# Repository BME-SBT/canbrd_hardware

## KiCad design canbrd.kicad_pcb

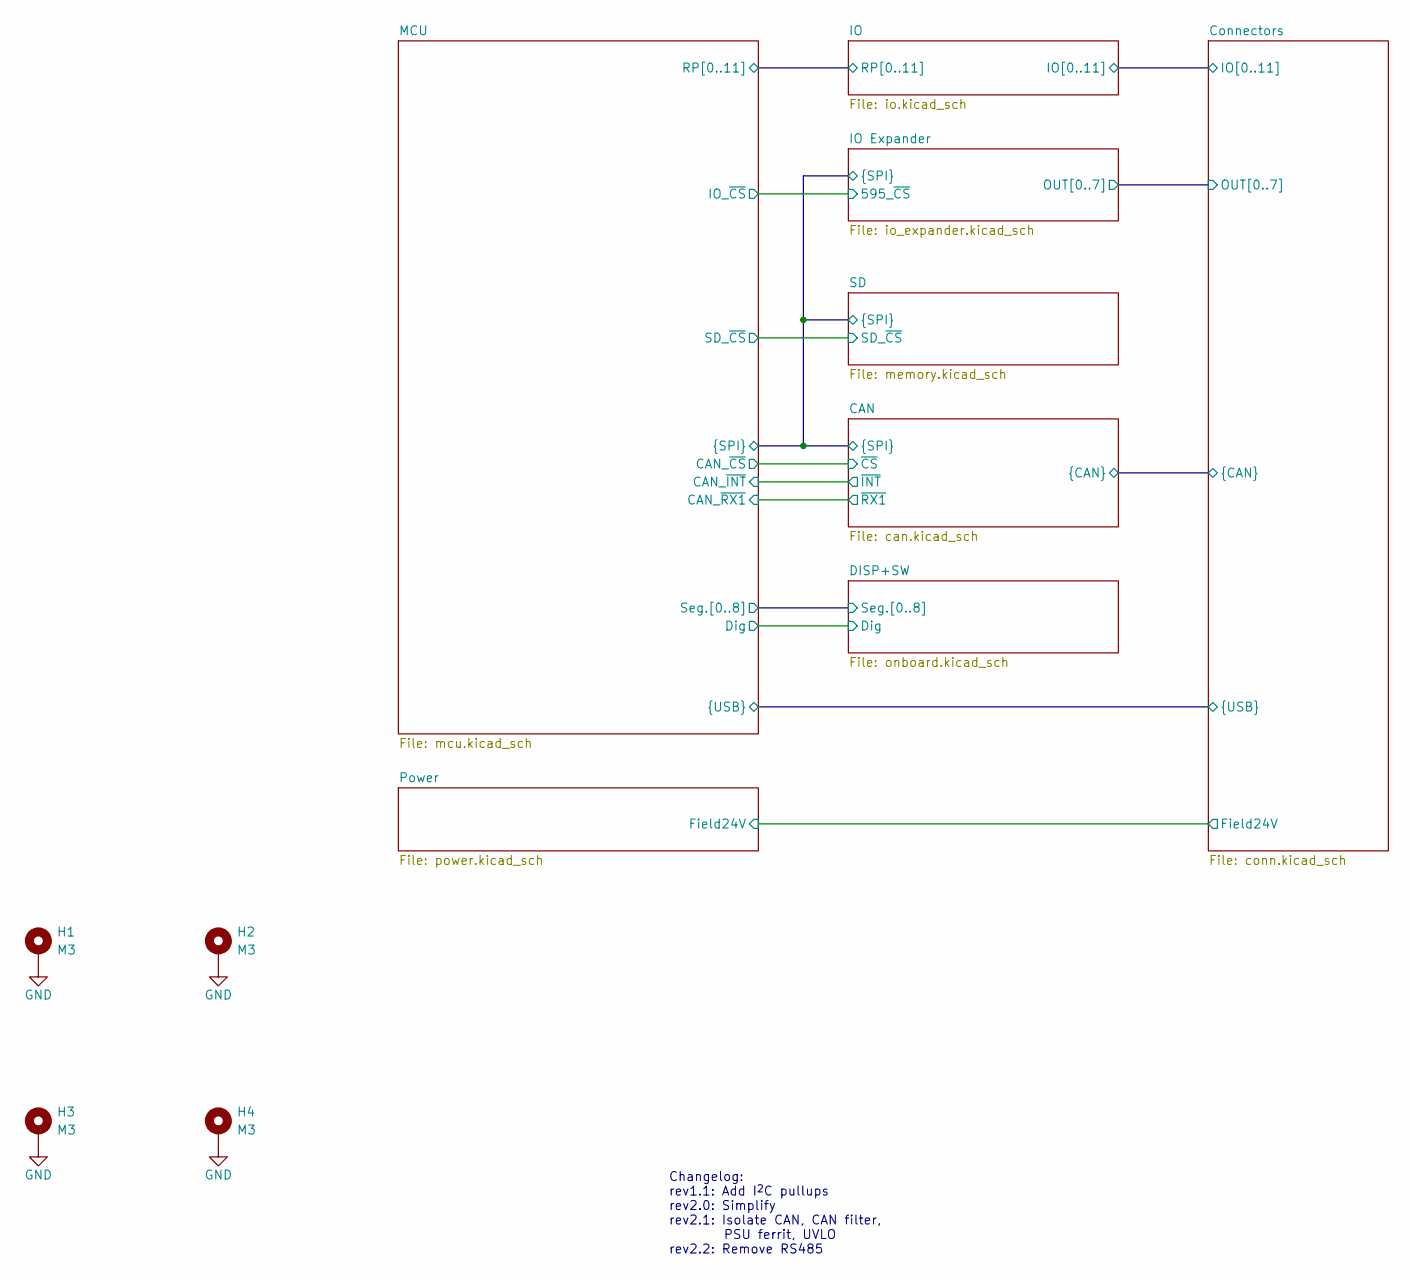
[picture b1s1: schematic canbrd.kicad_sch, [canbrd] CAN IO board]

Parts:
H1, H2, H3, H4: M3; MountingHole_3.2mm_M3_Pad_Via

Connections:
GND: H1.1, H2.1, H3.1, H4.1; also elsewhere on the board

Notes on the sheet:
Changelog: rev1.1: Add I^{2}C pullups rev2.0: Simplify rev2.1: Isolate CAN, CAN filter, PSU ferrit, UVLO rev2.2: Remove RS485

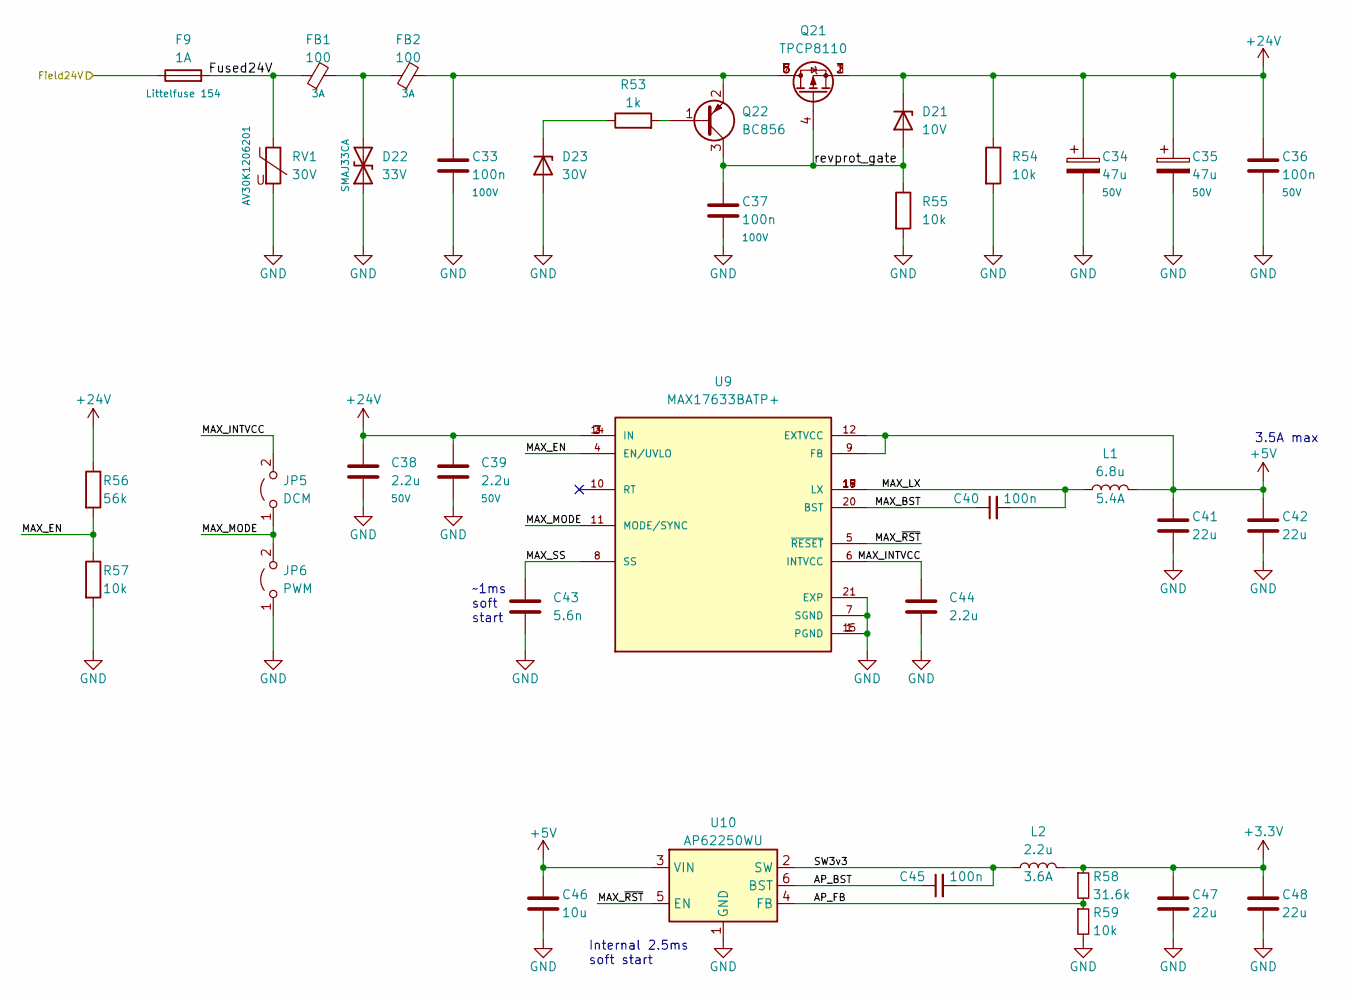
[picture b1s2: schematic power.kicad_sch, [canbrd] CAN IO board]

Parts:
C33, C37: 100n; C_1206_3216Metric; Voltage 100V
C34, C35: 47u; CP_Elec_8x6.5; Voltage 50V
C36: 100n; C_0805_2012Metric; Voltage 50V
C38, C39: 2.2u; C_1206_3216Metric; Voltage 50V
C40, C45: 100n; C_0603_1608Metric
C41, C42, C47, C48: 22u; C_0805_2012Metric
C43: 5.6n; C_0603_1608Metric
C44: 2.2u; C_0603_1608Metric
C46: 10u; C_0805_2012Metric
D21: 10V; D_SOD-123
D22: 33V; D_SMB
D23: 30V; D_SOD-123
F9: 1A; Littelfuse-154-2920
FB1, FB2: 100; L_1206_3216Metric
JP5: DCM; SolderJumper-2_P1.3mm_Open_TrianglePad1.0x1.5mm
JP6: PWM; SolderJumper-2_P1.3mm_Open_TrianglePad1.0x1.5mm
L1: 6.8u; L_Abracon_ASPI-0630LR
L2: 2.2u; L_Taiyo-Yuden_NR-50xx
Q21: TPCP8110; PS-8
Q22: BC856; SOT-23
R53: 1k; R_0603_1608Metric
R54, R55, R57, R59: 10k; R_0603_1608Metric
R56: 56k; R_0603_1608Metric
R58: 31.6k; R_0603_1608Metric
RV1: 30V; R_1206_3216Metric
U9: MAX17633BATP+; TQFN20-EP
U10: AP62250WU; TSOT26

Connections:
+3V3: C47.1, C48.1, L2.2, R58.1; also elsewhere on the board
+5V: C41.1, C42.1, C46.1, L1.2, U9.9 (FB), U9.12 (EXTVCC), U10.3 (VIN); also elsewhere on the board
+24V: C34.1, C35.1, C36.1, C38.1, C39.1, D21.1 (K), Q21.1 (S), Q21.2 (S), Q21.3 (S), R54.1, R56.1, U9.2 (IN), U9.3 (IN), U9.14 (IN); also elsewhere on the board
/Connectors/Field24V: F9.1; also elsewhere on the board
/Power/AP_BST: C45.1, U10.6 (BST)
/Power/AP_FB: R58.2, R59.1, U10.4 (FB)
/Power/Fused24V: F9.2, FB1.1, RV1.1
/Power/MAX_BST: C40.1, U9.20 (BST)
/Power/MAX_EN: R56.2, R57.1, U9.4 (EN/UVLO)
/Power/MAX_INTVCC: C44.1, JP5.2 (B), U9.6 (INTVCC)
/Power/MAX_LX: C40.2, L1.1, U9.17 (LX), U9.18 (LX), U9.19 (LX)
/Power/MAX_MODE: JP5.1 (A), JP6.2 (B), U9.11 (MODE/SYNC)
/Power/MAX_SS: C43.1, U9.8 (SS)
/Power/MAX_~RST: U9.5 (~RESET), U10.5 (EN)
/Power/SW3v3: C45.2, L2.1, U10.2 (SW)
/Power/revprot_gate: C37.1, D21.2 (A), Q21.4 (G), Q22.3 (C), R55.1
GND: C33.2, C34.2, C35.2, C36.2, C37.2, C38.2, C39.2, C41.2, C42.2, C43.2, C44.2, C46.2, C47.2, C48.2, D22.1 (A1), D23.2 (A), JP6.1 (A), R54.2, R55.2, R57.2, R59.2, RV1.2, U9.1 (PGND), U9.7 (SGND), U9.15 (PGND), U9.21 (EXP), U10.1 (GND); also elsewhere on the board
unnamed: C33.1, FB2.2, Q21.5 (D), Q21.6 (D), Q21.7 (D), Q21.8 (D), Q22.2 (E)
unnamed: D22.2 (A2), FB1.2, FB2.1
unnamed: D23.1 (K), R53.1
unnamed: Q22.1 (B), R53.2

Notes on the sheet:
~1ms soft start
3.5A max
Internal 2.5ms soft start

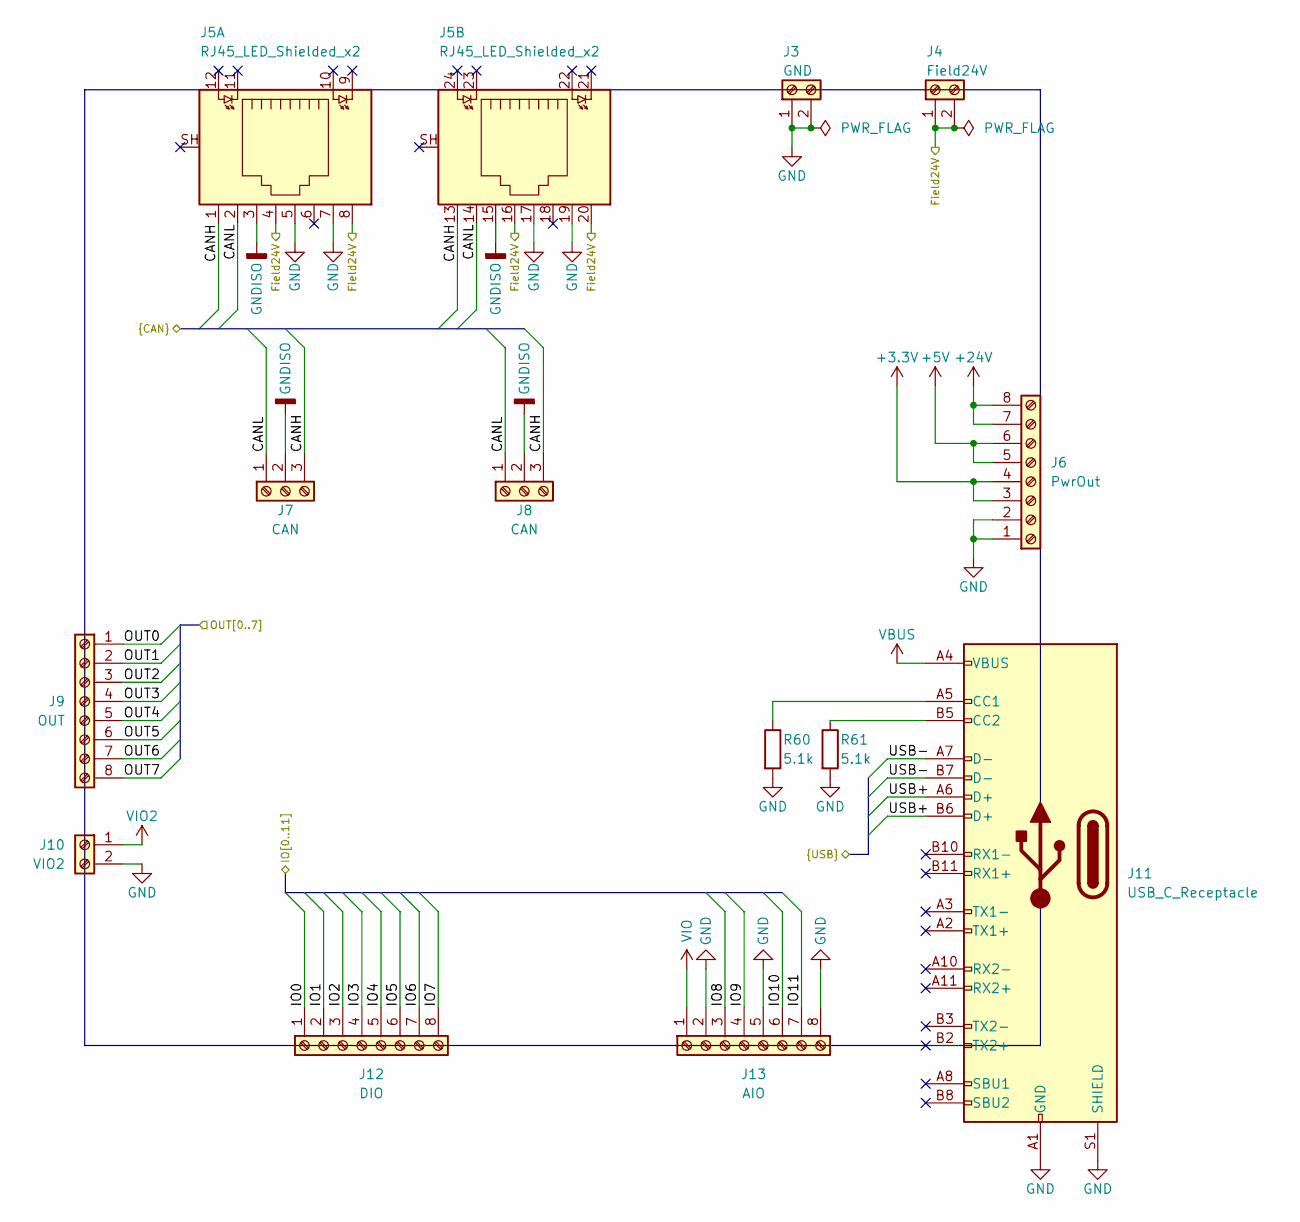
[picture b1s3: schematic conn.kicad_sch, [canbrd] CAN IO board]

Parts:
J3: GND; NH0210x0xxxxG
J4: Field24V; NH0210x0xxxxG
J5: RJ45_LED_Shielded_x2; RJ45_Amphenol_RJHSE5380-02
J6: PwrOut; NH0810x0xxxxG
J7, J8: CAN; NH0310x0xxxxG
J9: OUT; NH0810x0xxxxG
J10: VIO2; NH0210x0xxxxG
J11: USB_C_Receptacle; 10132328
J12: DIO; NH0810x0xxxxG
J13: AIO; NH0810x0xxxxG
R60, R61: 5.1k; R_0603_1608Metric

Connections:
+3V3: J6.3, J6.4; also elsewhere on the board
+5V: J6.5, J6.6; also elsewhere on the board
+24V: J6.7, J6.8; also elsewhere on the board
/CAN/CANH: J5.1, J5.13, J7.3, J8.3; also elsewhere on the board
/CAN/CANL: J5.2, J5.14, J7.1, J8.1; also elsewhere on the board
/Connectors/Field24V: J4.1, J4.2, J5.4, J5.8, J5.16, J5.20; also elsewhere on the board
/Connectors/IO0: J12.1; also elsewhere on the board
/Connectors/IO1: J12.2; also elsewhere on the board
/Connectors/IO2: J12.3; also elsewhere on the board
/Connectors/IO3: J12.4; also elsewhere on the board
/Connectors/IO4: J12.5; also elsewhere on the board
/Connectors/IO5: J12.6; also elsewhere on the board
/Connectors/IO6: J12.7; also elsewhere on the board
/Connectors/IO7: J12.8; also elsewhere on the board
/Connectors/IO8: J13.3; also elsewhere on the board
/Connectors/IO9: J13.4; also elsewhere on the board
/Connectors/IO10: J13.6; also elsewhere on the board
/Connectors/IO11: J13.7; also elsewhere on the board
/Connectors/OUT0: J9.1; also elsewhere on the board
/Connectors/OUT1: J9.2; also elsewhere on the board
/Connectors/OUT2: J9.3; also elsewhere on the board
/Connectors/OUT3: J9.4; also elsewhere on the board
/Connectors/OUT4: J9.5; also elsewhere on the board
/Connectors/OUT5: J9.6; also elsewhere on the board
/Connectors/OUT6: J9.7; also elsewhere on the board
/Connectors/OUT7: J9.8; also elsewhere on the board
/Connectors/USB+: J11.A6 (D+), J11.B6 (D+); also elsewhere on the board
/Connectors/USB-: J11.A7 (D-), J11.B7 (D-); also elsewhere on the board
GND: J3.1, J3.2, J5.5, J5.7, J5.17, J5.19, J6.1, J6.2, J10.2, J11.A1 (GND), J11.A12 (GND), J11.B1 (GND), J11.B12 (GND), J11.S1 (SHIELD), J13.2, J13.5, J13.8, R60.2, R61.2; also elsewhere on the board
GNDISO: J5.3, J5.15, J7.2, J8.2; also elsewhere on the board
unnamed: J11.A5 (CC1), R60.1
unnamed: J11.B5 (CC2), R61.1
VBUS: J11.A4 (VBUS), J11.A9 (VBUS), J11.B4 (VBUS), J11.B9 (VBUS)
VIO: J13.1; also elsewhere on the board
VIO2: J10.1; also elsewhere on the board

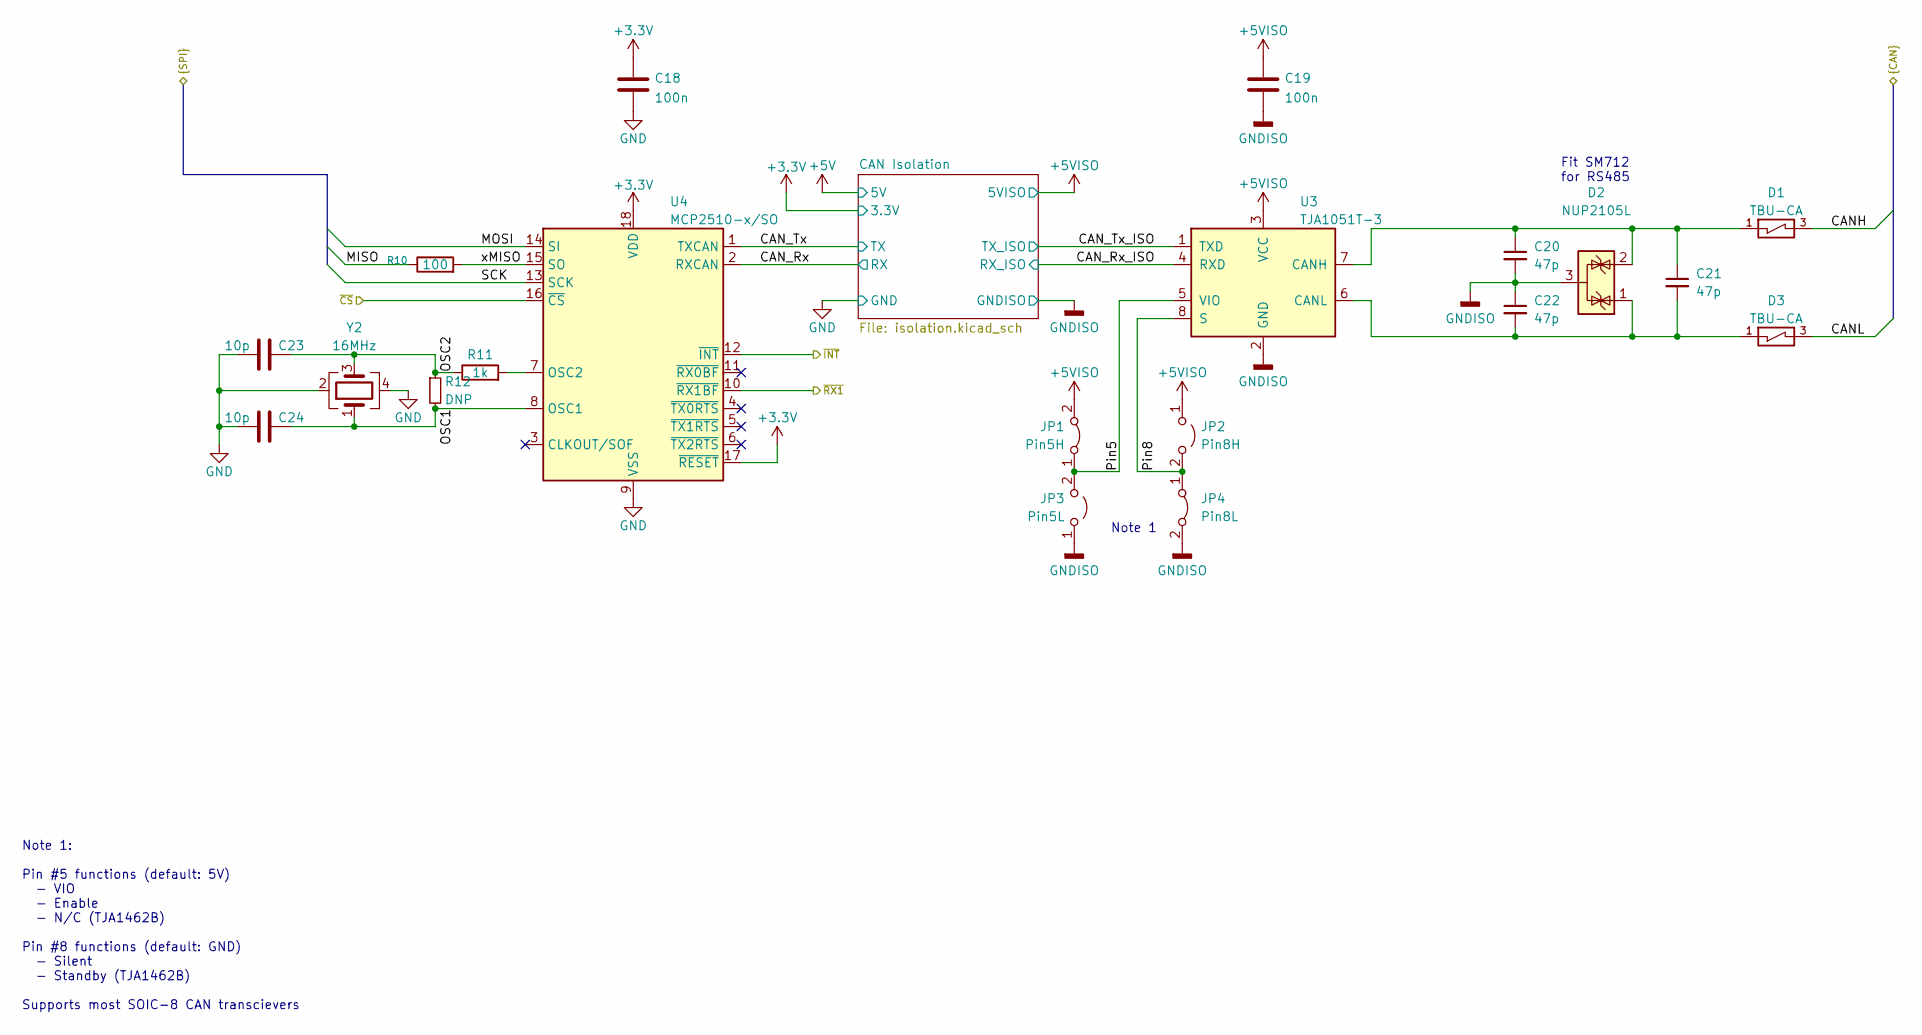
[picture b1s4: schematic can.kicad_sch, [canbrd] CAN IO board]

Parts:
C18, C19: 100n; C_0603_1608Metric
C20, C21, C22: 47p; C_0603_1608Metric
C23, C24: 10p; C_0603_1608Metric
D1, D3: TBU-CA; DIOC650X400X100N
D2: NUP2105L; SOT-23
JP1: Pin5H; SolderJumper-2_P1.3mm_Bridged_Pad1.0x1.5mm
JP2: Pin8H; SolderJumper-2_P1.3mm_Open_TrianglePad1.0x1.5mm
JP3: Pin5L; SolderJumper-2_P1.3mm_Open_TrianglePad1.0x1.5mm
JP4: Pin8L; SolderJumper-2_P1.3mm_Bridged_Pad1.0x1.5mm
R10: 100; R_0603_1608Metric
R11: 1k; R_0603_1608Metric
R12: DNP; R_0603_1608Metric
U3: TJA1051T-3; SOIC-8_3.9x4.9mm_P1.27mm
U4: MCP2510-x/SO; SOIC-18W_7.5x11.6mm_P1.27mm
Y2: 16MHz; Crystal_SMD_3225-4Pin_3.2x2.5mm

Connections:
+3V3: C18.1, U4.17 (~RESET), U4.18 (VDD); also elsewhere on the board
+5VISO: C19.1, JP1.2 (B), JP2.1 (A), U3.3 (VCC); also elsewhere on the board
/CAN/CANH: D1.3; also elsewhere on the board
/CAN/CANL: D3.3; also elsewhere on the board
/CAN/CAN_Rx: U4.2 (RXCAN); also elsewhere on the board
/CAN/CAN_Rx_ISO: U3.4 (RXD); also elsewhere on the board
/CAN/CAN_Tx: U4.1 (TXCAN); also elsewhere on the board
/CAN/CAN_Tx_ISO: U3.1 (TXD); also elsewhere on the board
/CAN/MISO: R10.1; also elsewhere on the board
/CAN/MOSI: U4.14 (SI); also elsewhere on the board
/CAN/OSC1: C24.2, R12.2, U4.8 (OSC1), Y2.1
/CAN/OSC2: C23.2, R11.1, R12.1, Y2.3
/CAN/Pin5: JP1.1 (A), JP3.2 (B), U3.5 (VIO)
/CAN/Pin8: JP2.2 (B), JP4.1 (A), U3.8 (S)
/CAN/SCK: U4.13 (SCK); also elsewhere on the board
/CAN/xMISO: R10.2, U4.15 (SO)
/CAN/~CS: U4.16 (~CS); also elsewhere on the board
/CAN/~INT: U4.12 (~INT); also elsewhere on the board
/CAN/~RX1: U4.10 (~RX1BF); also elsewhere on the board
GND: C18.2, C23.1, C24.1, U4.9 (VSS), Y2.2, Y2.4; also elsewhere on the board
GNDISO: C19.2, C20.2, C22.1, D2.3 (A), JP3.1 (A), JP4.2 (B), U3.2 (GND); also elsewhere on the board
unnamed: C20.1, C21.1, D1.1, D2.2 (K), U3.7 (CANH)
unnamed: C21.2, C22.2, D2.1 (K), D3.1, U3.6 (CANL)
unnamed: R11.2, U4.7 (OSC2)

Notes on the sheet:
Note 1: Pin #5 functions (default: 5V) - VIO - Enable - N/C (TJA1462B) Pin #8 functions (default: GND) - Silent - Standby (TJA1462B) Supports most SOIC-8 CAN transcievers
Note 1
Fit SM712 for RS485

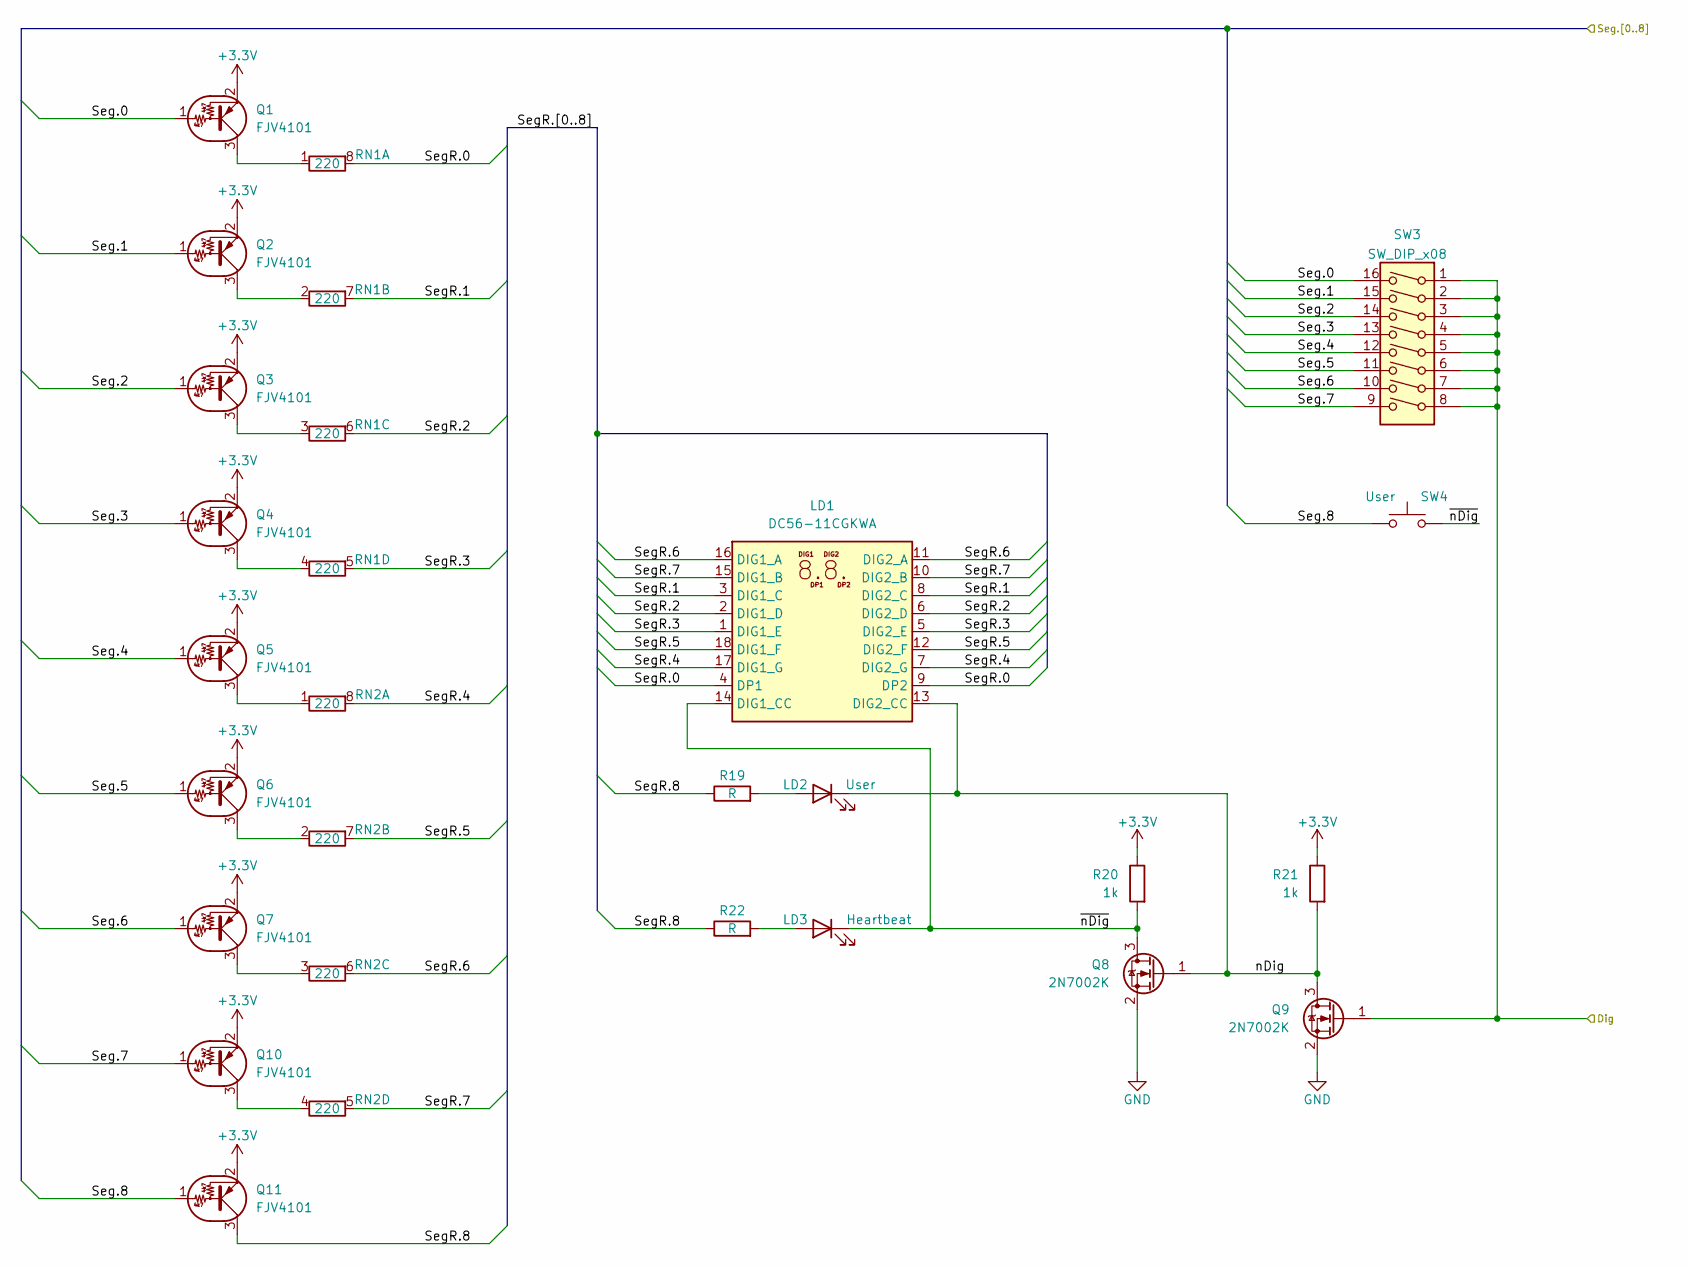
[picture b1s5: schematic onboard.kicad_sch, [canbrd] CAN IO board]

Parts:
LD1: DC56-11CGKWA; LB-402
LD2: User; LED_0805_2012Metric
LD3: Heartbeat; LED_0805_2012Metric
Q1, Q2, Q3, Q4, Q5, Q6, Q7, Q10, Q11: FJV4101; SOT-23
Q8, Q9: 2N7002K; SOT-23
R19, R22: R; R_0603_1608Metric
R20, R21: 1k; R_0603_1608Metric
RN1, RN2: 220; R_Array_Convex_4x0603
SW3: SW_DIP_x08; SW_DIP_SPSTx08_Slide_KingTek_DSHP08TS_W7.62mm_P1.27mm
SW4: User; PTS815-SJ

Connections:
+3V3: Q1.2 (E), Q2.2 (E), Q3.2 (E), Q4.2 (E), Q5.2 (E), Q6.2 (E), Q7.2 (E), Q10.2 (E), Q11.2 (E), R20.1, R21.1; also elsewhere on the board
/DISP+SW/Dig: Q9.1 (G), SW3.1, SW3.2, SW3.3, SW3.4, SW3.5, SW3.6, SW3.7, SW3.8; also elsewhere on the board
/DISP+SW/Seg.0: Q1.1 (B), SW3.16; also elsewhere on the board
/DISP+SW/Seg.1: Q2.1 (B), SW3.15; also elsewhere on the board
/DISP+SW/Seg.2: Q3.1 (B), SW3.14; also elsewhere on the board
/DISP+SW/Seg.3: Q4.1 (B), SW3.13; also elsewhere on the board
/DISP+SW/Seg.4: Q5.1 (B), SW3.12; also elsewhere on the board
/DISP+SW/Seg.5: Q6.1 (B), SW3.11; also elsewhere on the board
/DISP+SW/Seg.6: Q7.1 (B), SW3.10; also elsewhere on the board
/DISP+SW/Seg.7: Q10.1 (B), SW3.9; also elsewhere on the board
/DISP+SW/Seg.8: Q11.1 (B), SW4.2; also elsewhere on the board
/DISP+SW/SegR.0: LD1.4 (DP1), LD1.9 (DP2), RN1.8 (R1.2)
/DISP+SW/SegR.1: LD1.3 (DIG1_C), LD1.8 (DIG2_C), RN1.7 (R2.2)
/DISP+SW/SegR.2: LD1.2 (DIG1_D), LD1.6 (DIG2_D), RN1.6 (R3.2)
/DISP+SW/SegR.3: LD1.1 (DIG1_E), LD1.5 (DIG2_E), RN1.5 (R4.2)
/DISP+SW/SegR.4: LD1.7 (DIG2_G), LD1.17 (DIG1_G), RN2.8 (R1.2)
/DISP+SW/SegR.5: LD1.12 (DIG2_F), LD1.18 (DIG1_F), RN2.7 (R2.2)
/DISP+SW/SegR.6: LD1.11 (DIG2_A), LD1.16 (DIG1_A), RN2.6 (R3.2)
/DISP+SW/SegR.7: LD1.10 (DIG2_B), LD1.15 (DIG1_B), RN2.5 (R4.2)
/DISP+SW/SegR.8: Q11.3 (C), R19.1, R22.1
/DISP+SW/nDig: LD1.13 (DIG2_CC), LD2.1 (K), Q8.1 (G), Q9.3 (D), R21.2
/DISP+SW/~nDig: LD1.14 (DIG1_CC), LD3.1 (K), Q8.3 (D), R20.2, SW4.1
GND: Q8.2 (S), Q9.2 (S); also elsewhere on the board
unnamed: LD2.2 (A), R19.2
unnamed: LD3.2 (A), R22.2
unnamed: Q1.3 (C), RN1.1 (R1.1)
unnamed: Q2.3 (C), RN1.2 (R2.1)
unnamed: Q3.3 (C), RN1.3 (R3.1)
unnamed: Q4.3 (C), RN1.4 (R4.1)
unnamed: Q5.3 (C), RN2.1 (R1.1)
unnamed: Q6.3 (C), RN2.2 (R2.1)
unnamed: Q7.3 (C), RN2.3 (R3.1)
unnamed: Q10.3 (C), RN2.4 (R4.1)

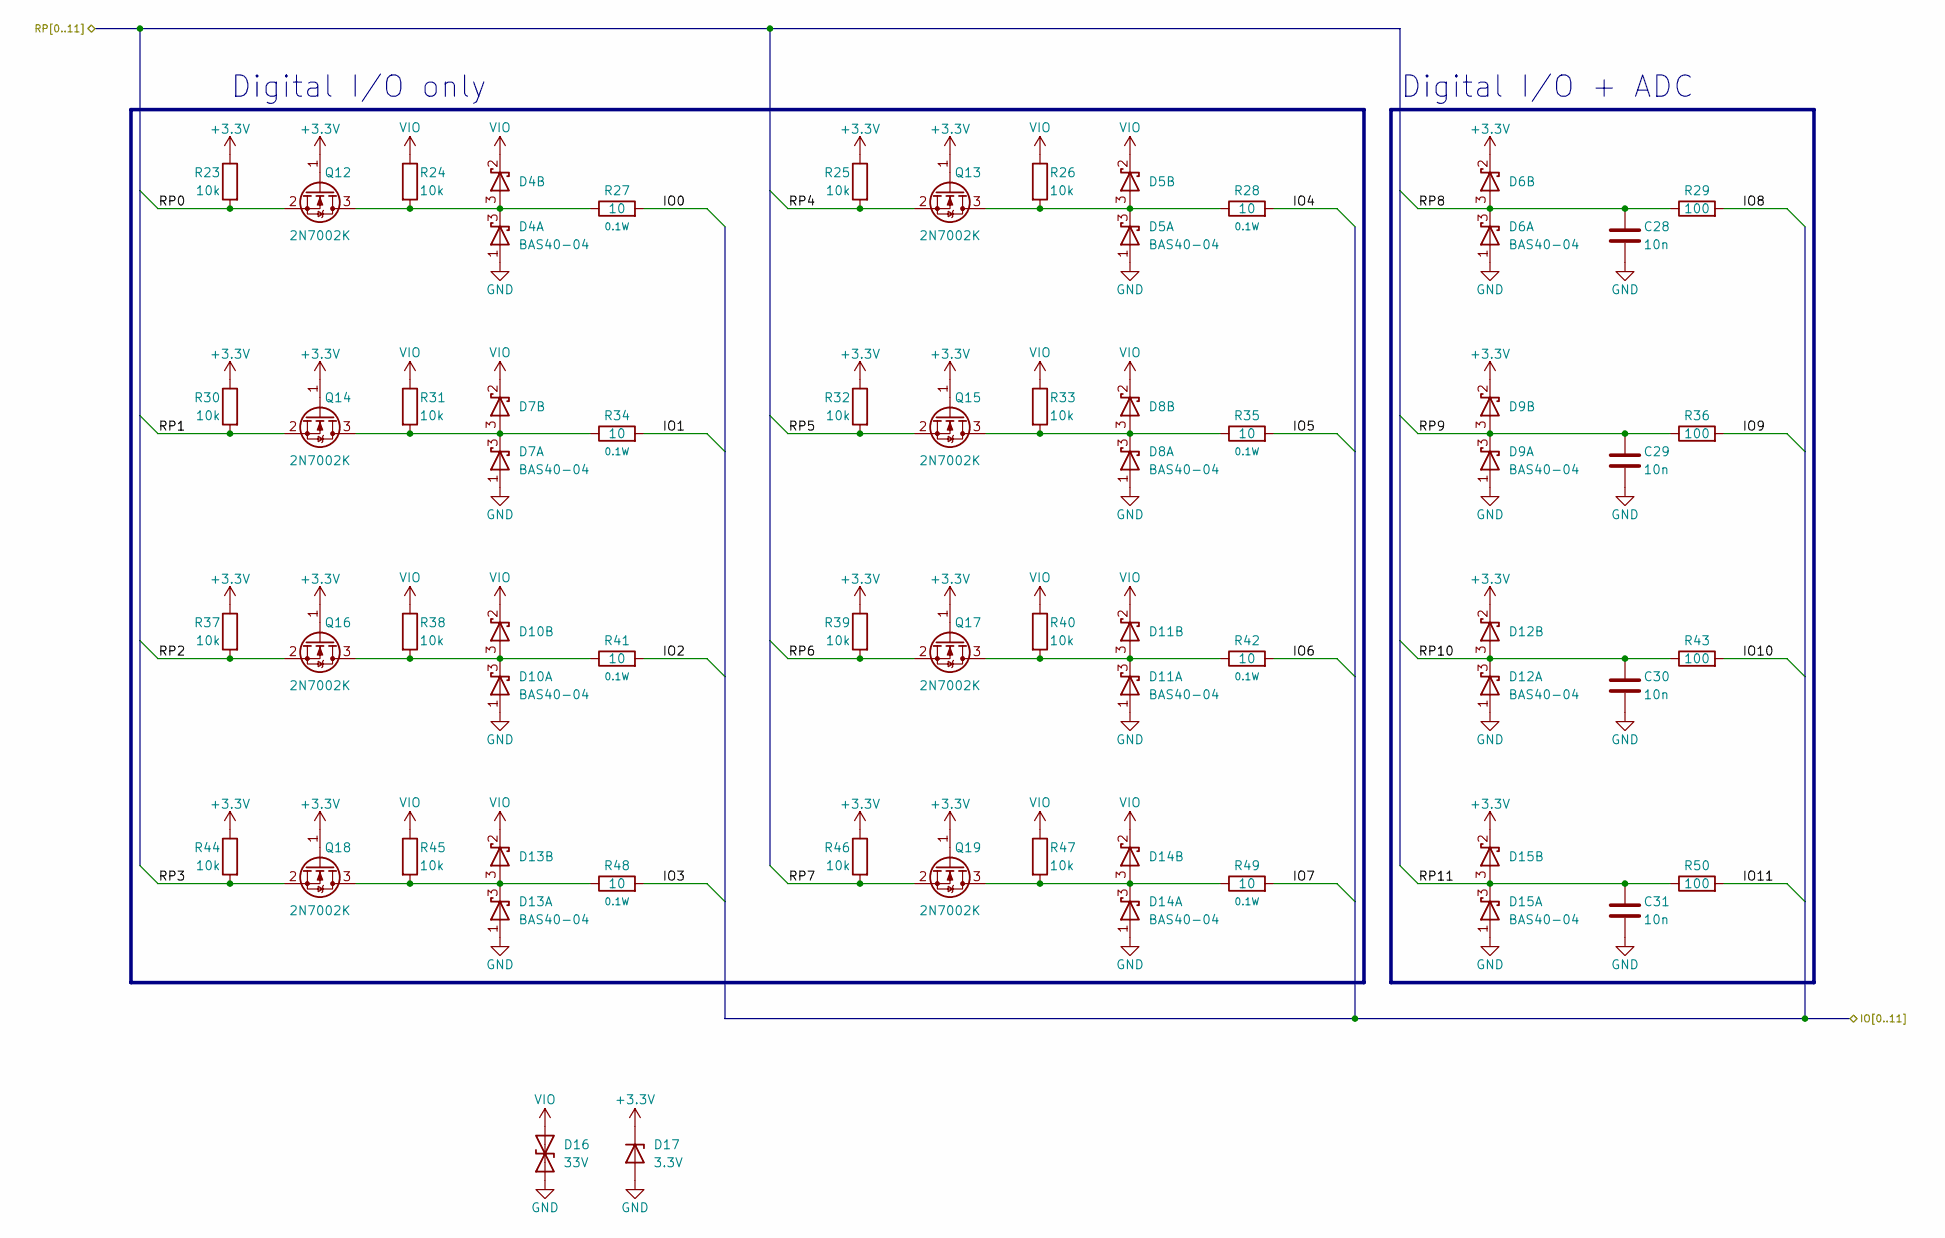
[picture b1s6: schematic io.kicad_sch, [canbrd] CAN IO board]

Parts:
C28, C29, C30, C31: 10n; C_0603_1608Metric
D4, D5, D6, D7, D8, D9, D10, D11, D12, D13, D14, D15: BAS40-04; SOT-23
D16: 33V; D_SMB
D17: 3.3V; D_MiniMELF
Q12, Q13, Q14, Q15, Q16, Q17, Q18, Q19: 2N7002K; SOT-23
R23, R24, R25, R26, R30, R31, R32, R33, R37, R38, R39, R40, R44, R45, R46, R47: 10k; R_0603_1608Metric
R27, R28, R34, R35, R41, R42, R48, R49: 10; R_0603_1608Metric
R29, R36, R43, R50: 100; R_0603_1608Metric

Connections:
+3V3: D6.2 (K), D9.2 (K), D12.2 (K), D15.2 (K), D17.1 (K), Q12.1 (G), Q13.1 (G), Q14.1 (G), Q15.1 (G), Q16.1 (G), Q17.1 (G), Q18.1 (G), Q19.1 (G), R23.1, R25.1, R30.1, R32.1, R37.1, R39.1, R44.1, R46.1; also elsewhere on the board
/Connectors/IO0: R27.2; also elsewhere on the board
/Connectors/IO1: R34.2; also elsewhere on the board
/Connectors/IO2: R41.2; also elsewhere on the board
/Connectors/IO3: R48.2; also elsewhere on the board
/Connectors/IO4: R28.2; also elsewhere on the board
/Connectors/IO5: R35.2; also elsewhere on the board
/Connectors/IO6: R42.2; also elsewhere on the board
/Connectors/IO7: R49.2; also elsewhere on the board
/Connectors/IO8: R29.2; also elsewhere on the board
/Connectors/IO9: R36.2; also elsewhere on the board
/Connectors/IO10: R43.2; also elsewhere on the board
/Connectors/IO11: R50.2; also elsewhere on the board
/IO/RP0: Q12.2 (S), R23.2; also elsewhere on the board
/IO/RP1: Q14.2 (S), R30.2; also elsewhere on the board
/IO/RP2: Q16.2 (S), R37.2; also elsewhere on the board
/IO/RP3: Q18.2 (S), R44.2; also elsewhere on the board
/IO/RP4: Q13.2 (S), R25.2; also elsewhere on the board
/IO/RP5: Q15.2 (S), R32.2; also elsewhere on the board
/IO/RP6: Q17.2 (S), R39.2; also elsewhere on the board
/IO/RP7: Q19.2 (S), R46.2; also elsewhere on the board
/IO/RP8: C28.1, D6.3 (K), R29.1; also elsewhere on the board
/IO/RP9: C29.1, D9.3 (K), R36.1; also elsewhere on the board
/IO/RP10: C30.1, D12.3 (K), R43.1; also elsewhere on the board
/IO/RP11: C31.1, D15.3 (K), R50.1; also elsewhere on the board
GND: C28.2, C29.2, C30.2, C31.2, D4.1 (A), D5.1 (A), D6.1 (A), D7.1 (A), D8.1 (A), D9.1 (A), D10.1 (A), D11.1 (A), D12.1 (A), D13.1 (A), D14.1 (A), D15.1 (A), D16.1 (A1), D17.2 (A); also elsewhere on the board
unnamed: D4.3 (K), Q12.3 (D), R24.2, R27.1
unnamed: D5.3 (K), Q13.3 (D), R26.2, R28.1
unnamed: D7.3 (K), Q14.3 (D), R31.2, R34.1
unnamed: D8.3 (K), Q15.3 (D), R33.2, R35.1
unnamed: D10.3 (K), Q16.3 (D), R38.2, R41.1
unnamed: D11.3 (K), Q17.3 (D), R40.2, R42.1
unnamed: D13.3 (K), Q18.3 (D), R45.2, R48.1
unnamed: D14.3 (K), Q19.3 (D), R47.2, R49.1
VIO: D4.2 (K), D5.2 (K), D7.2 (K), D8.2 (K), D10.2 (K), D11.2 (K), D13.2 (K), D14.2 (K), D16.2 (A2), R24.1, R26.1, R31.1, R33.1, R38.1, R40.1, R45.1, R47.1; also elsewhere on the board

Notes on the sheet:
Digital I/O only
Digital I/O + ADC

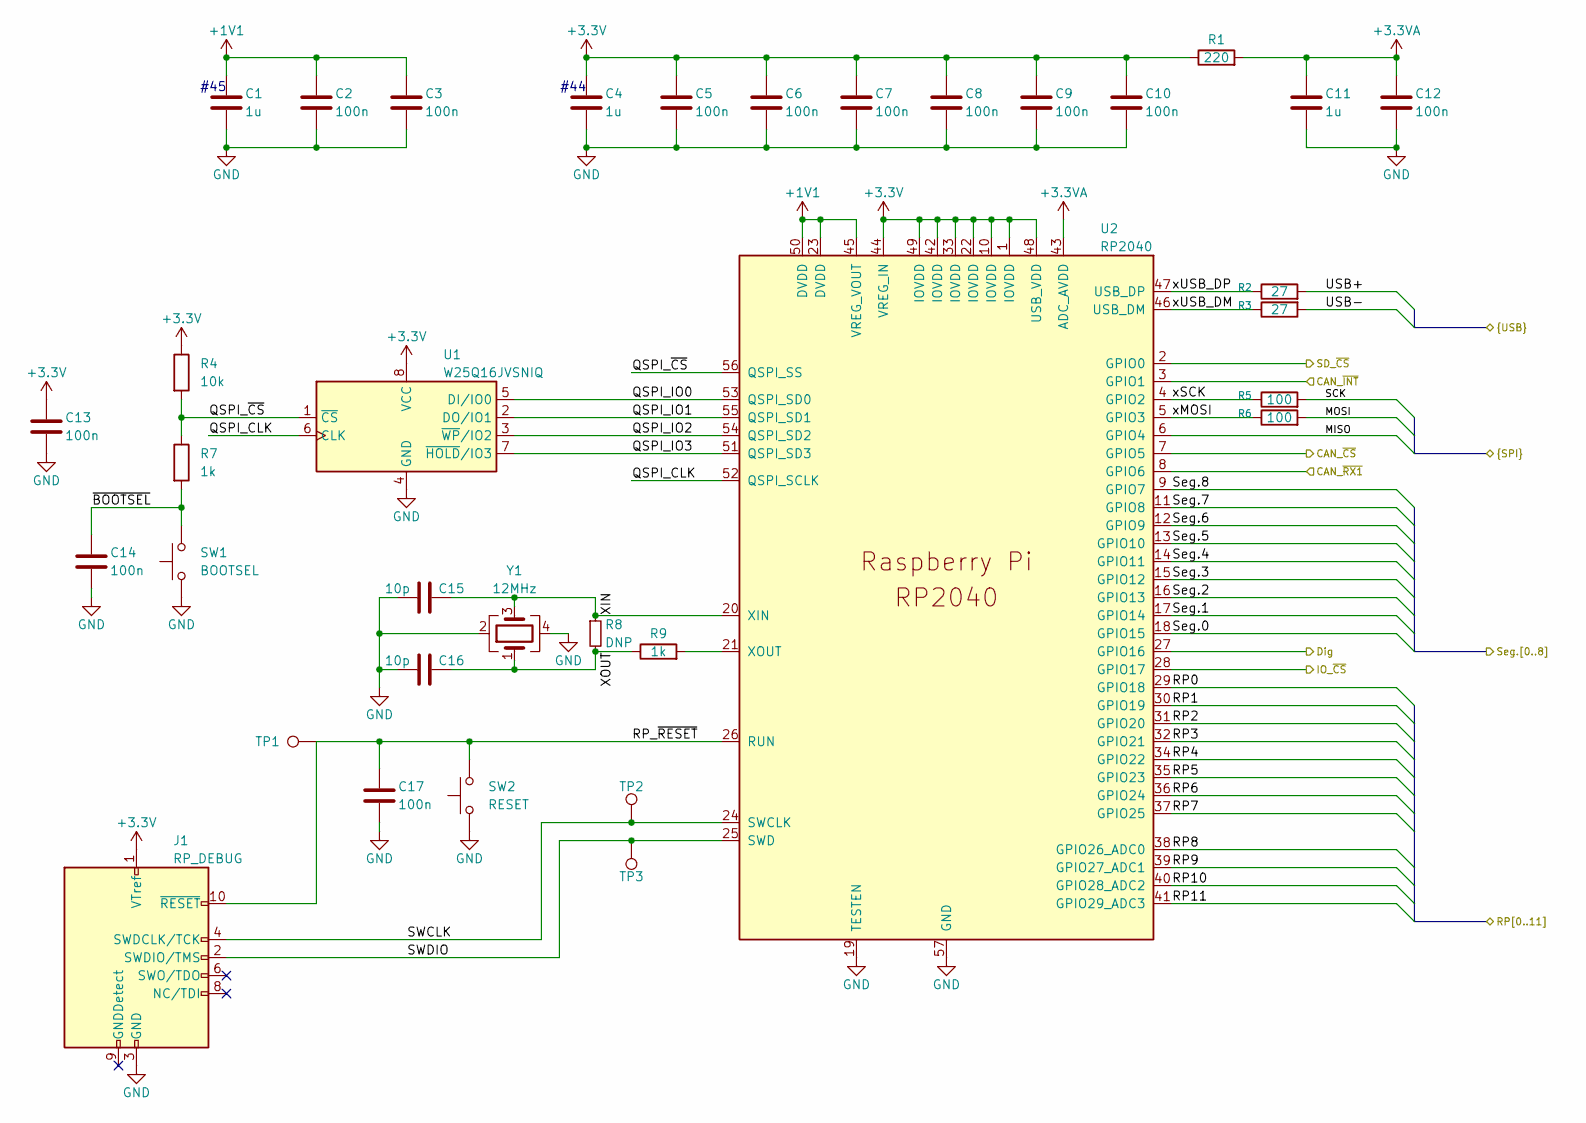
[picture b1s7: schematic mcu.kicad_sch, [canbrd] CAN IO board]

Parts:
C1, C4, C11: 1u; C_0603_1608Metric
C2, C3, C5, C6, C7, C8, C9, C10, C12, C13, C14, C17: 100n; C_0603_1608Metric
C15, C16: 10p; C_0603_1608Metric
J1: RP_DEBUG; PinHeader_2x05_P1.27mm_Vertical_SMD
R1: 220; R_0603_1608Metric
R2, R3: 27; R_0603_1608Metric
R4: 10k; R_0603_1608Metric
R5, R6: 100; R_0603_1608Metric
R7, R9: 1k; R_0603_1608Metric
R8: DNP; R_0603_1608Metric
SW1: BOOTSEL; PTS815-SJ
SW2: RESET; PTS815-SJ
TP1, TP2, TP3: TestPoint; TestPoint_THTPad_D2.0mm_Drill1.0mm
U1: W25Q16JVSNIQ; SOIC-8_3.9x4.9mm_P1.27mm
U2: RP2040; RP2040-QFN-56
Y1: 12MHz; Crystal_SMD_3225-4Pin_3.2x2.5mm

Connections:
+1V1: C1.1, C2.1, C3.1, U2.23 (DVDD), U2.45 (VREG_VOUT), U2.50 (DVDD)
+3.3VA: C11.1, C12.1, R1.2, U2.43 (ADC_AVDD)
+3V3: C4.1, C5.1, C6.1, C7.1, C8.1, C9.1, C10.1, C13.1, J1.1 (VTref), R1.1, R4.1, U1.8 (VCC), U2.1 (IOVDD), U2.10 (IOVDD), U2.22 (IOVDD), U2.33 (IOVDD), U2.42 (IOVDD), U2.44 (VREG_IN), U2.48 (USB_VDD), U2.49 (IOVDD); also elsewhere on the board
/CAN/MISO: U2.6 (GPIO4); also elsewhere on the board
/CAN/MOSI: R6.2; also elsewhere on the board
/CAN/SCK: R5.2; also elsewhere on the board
/CAN/~CS: U2.7 (GPIO5); also elsewhere on the board
/CAN/~INT: U2.3 (GPIO1); also elsewhere on the board
/CAN/~RX1: U2.8 (GPIO6); also elsewhere on the board
/Connectors/USB+: R2.2; also elsewhere on the board
/Connectors/USB-: R3.2; also elsewhere on the board
/DISP+SW/Dig: U2.27 (GPIO16); also elsewhere on the board
/DISP+SW/Seg.0: U2.18 (GPIO15); also elsewhere on the board
/DISP+SW/Seg.1: U2.17 (GPIO14); also elsewhere on the board
/DISP+SW/Seg.2: U2.16 (GPIO13); also elsewhere on the board
/DISP+SW/Seg.3: U2.15 (GPIO12); also elsewhere on the board
/DISP+SW/Seg.4: U2.14 (GPIO11); also elsewhere on the board
/DISP+SW/Seg.5: U2.13 (GPIO10); also elsewhere on the board
/DISP+SW/Seg.6: U2.12 (GPIO9); also elsewhere on the board
/DISP+SW/Seg.7: U2.11 (GPIO8); also elsewhere on the board
/DISP+SW/Seg.8: U2.9 (GPIO7); also elsewhere on the board
/IO Expander/595_~CS: U2.28 (GPIO17); also elsewhere on the board
/IO/RP0: U2.29 (GPIO18); also elsewhere on the board
/IO/RP1: U2.30 (GPIO19); also elsewhere on the board
/IO/RP2: U2.31 (GPIO20); also elsewhere on the board
/IO/RP3: U2.32 (GPIO21); also elsewhere on the board
/IO/RP4: U2.34 (GPIO22); also elsewhere on the board
/IO/RP5: U2.35 (GPIO23); also elsewhere on the board
/IO/RP6: U2.36 (GPIO24); also elsewhere on the board
/IO/RP7: U2.37 (GPIO25); also elsewhere on the board
/IO/RP8: U2.38 (GPIO26_ADC0); also elsewhere on the board
/IO/RP9: U2.39 (GPIO27_ADC1); also elsewhere on the board
/IO/RP10: U2.40 (GPIO28_ADC2); also elsewhere on the board
/IO/RP11: U2.41 (GPIO29_ADC3); also elsewhere on the board
/MCU/QSPI_CLK: U1.6 (CLK), U2.52 (QSPI_SCLK)
/MCU/QSPI_IO0: U1.5 (DI/IO0), U2.53 (QSPI_SD0)
/MCU/QSPI_IO1: U1.2 (DO/IO1), U2.55 (QSPI_SD1)
/MCU/QSPI_IO2: U1.3 (~WP/IO2), U2.54 (QSPI_SD2)
/MCU/QSPI_IO3: U1.7 (~HOLD/IO3), U2.51 (QSPI_SD3)
/MCU/QSPI_~CS: R4.2, R7.1, U1.1 (~CS), U2.56 (QSPI_SS)
/MCU/RP_~RESET: C17.1, J1.10 (~RESET), SW2.2, TP1.1, U2.26 (RUN)
/MCU/SD_~CS: U2.2 (GPIO0); also elsewhere on the board
/MCU/SWCLK: J1.4 (SWDCLK/TCK), TP2.1, U2.24 (SWCLK)
/MCU/SWDIO: J1.2 (SWDIO/TMS), TP3.1, U2.25 (SWD)
/MCU/XIN: C15.2, R8.1, U2.20 (XIN), Y1.3
/MCU/XOUT: C16.2, R8.2, R9.1, Y1.1
/MCU/xMOSI: R6.1, U2.5 (GPIO3)
/MCU/xSCK: R5.1, U2.4 (GPIO2)
/MCU/xUSB_DM: R3.1, U2.46 (USB_DM)
/MCU/xUSB_DP: R2.1, U2.47 (USB_DP)
/MCU/~BOOTSEL: C14.1, R7.2, SW1.1
GND: C1.2, C2.2, C3.2, C4.2, C5.2, C6.2, C7.2, C8.2, C9.2, C10.2, C11.2, C12.2, C13.2, C14.2, C15.1, C16.1, C17.2, J1.3 (GND), J1.5 (GND), SW1.2, SW2.1, U1.4 (GND), U2.19 (TESTEN), U2.57 (GND), Y1.2, Y1.4; also elsewhere on the board
unnamed: R9.2, U2.21 (XOUT)

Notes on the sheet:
#45
#44
